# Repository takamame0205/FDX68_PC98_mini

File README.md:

# PC-98用 FDX68/FDD 簡易切り替えボード

<b>1. 概要</b><BR>
NECのPC-9800シリーズにGIMONS氏開発のフロッピーエミュレーターFDX68を接続し、実FDDと併用するための実験用ボードです。FDX68のエミュレーションモードおよびコントローラーモードをサポートしており、実FDDとしては3.5インチ(3モード可)×1台、あるいは3.5インチ1台+5インチ1台での使用を想定しています。ミカエル氏のFDS+と比べると低機能ですが、その分簡単に製作でき、DIP品のICのみで設計してあるのにもかかわらず小型化することができました。なお、このボードは私個人が研究目的で作成したもので開発途上のものです。ちなみにこちらでは、PC-9801BX3(CPUをDX4ODP-100MHzに換装)にFD1148TとFD1155Dを接続し、FDX68 Version 1.2A (fdrestore のみ 1.3)、RasPi OS buster 2021-01-11版使用にて動作確認を行っています。<br><br>

<b>2. 制限事項</b><BR>
このボードは簡素なつくりのため、FDS+と比べ機能制限が多いです。エミュレーションモードでのドライブ番号(0のみ、1のみ、0/1両方)はジャンパーで設定するようになっており、動的な変更はできません(もちろん、このジャンパーのピンヘッダ―に双極双投のトグルスイッチなどを接続すれば外部から切り替えることは可能です)。また、5インチドライブとして<b>ターミネーション抵抗値の低いFD1155Dなどを使用した場合に動作が不安定になる可能性</b>があります(対処法は下に記します)。<br><br>

<b>3. 免責など</b><br>
ここで公開している内容はありのまま(As Is)で提供するものであり、動作を保証するものではありません。また、使用したことによりお手持ちの機器(PC本体、FDX68、FDDなど)にダメージを与える可能性もあります。私個人が金銭的、身体的損害について補償することはできませんので、ご利用は個人の責任において行ってください。<br><br>
  
<b>4. ファイルの配置</b><BR>
KiCad : KiCadプロジェクトファイル<BR>
KiCad/garber : ガーバーファイル<BR>
Tiny13 : マイコン(ATtiny13A)のファームウェア(AtmelStudio用ソース)<BR>
Firmware : マイコン(ATtiny13A)のファームウェア(Intel Hex形式バイナリ)<BR>
　ヒューズ設定データはfuse.hex<BR>
　設定内容 : CKSEL = 01 (4.8MHz), CKDIV8 = 0 (600KHz)<br>
　　SUT = 10 (Slow Start), WDTON = 1 (WDT OFF)<br>
preview.png : 基板のプレビューイメージ<BR>
scheme.png : 基板回路図<BR><br>

<b>5. 部品一覧</b><br>
コネクター<br>
J1, J2：2.54mmピッチ 2x15pin ボックスヘッダー<br>
J3, J4：2.54mmピッチ 2x17pin ボックスヘッダー<br>
J5：2.54mmピッチ 5pin ライトアングルピンヘッダ―<br><br>
コンデンサー<br>
C1：47μF 25V アルミ電解コンデンサー<br>
C2, C3, C4：0.1μF 50V (積層)セラミックコンデンサー<br><br>
抵抗<br>
R1, R3：22kΩ<br>
R2：220Ω～270Ω (LEDの電流制限抵抗なので、使用するLEDによって適宜調整してください)<br><br>
IC<br>
  U1, U2：74HC4066 (<b>ON抵抗の低いもの</b>を選んでください)<br>
U3：ATtiny13A<br><br>
ダイオード<br>
D5, D6：BAT43 (Vfの小さいSBDを使用しています)<br><br>
ジャンパー<br>
JP2, 3：2.54mmピッチ 3pin ストレートピンヘッダー<br>
JP7：2.54mmピッチ 2pin ストレートピンヘッダー<br><br>

<b>6. 接続方法</b><BR>
マザーボードとの接続用(J1)および3.5インチFDD接続用(J2)のコネクターは30ピンタイプ(A-MateやFellowのマザーボードコネクターと同じタイプ)を、FDX68接続用(J3)および5インチFDD接続用(J4)のコネクターは34ピンタイプ(一般的なマザーボード上34ピンFDDコネクターと同じタイプ)を使用しています。いずれも左上(印のついている)ピンが1番ピンになっていますので、向きを間違えないように接続してください。J1, J3には<b>反転していない</b>ストレートのケーブルを使用します。FDX68のコネクターは一般的なPC-98用3.5インチFDDとは向きが逆になっていますので注意してください。マザーボードとの接続は、同じ30ピンのコネクターを搭載している機種であれば単純なストレートのケーブルでOKですが、34ピンのコネクター搭載機種だと変換ケーブルの作成が必要です。その場合、基板への電源供給ができませんので、変換ケーブルを作成する際にVCCピン(1,3,5)に電源を接続するか、操作スイッチなどを接続するJ5のVCC("+"表示のある1番ピン)から電源を供給するようにしてください。<BR><BR>
なお、J5(操作スイッチ接続コネクター)のピンアサインは下記のとおりです。<BR><BR>
Pin 1 (+) : VCC (J1のVCCピンと直結)<BR>
Pin 2 (L) : モード表示LED出力(Active Low)<BR>
Pin 3 (S) : 操作ボタン入力(Active Low)<BR>
Pin 4 (I) : RasPi電源検知入力(Active High)<BR>
Pin 5 (-) : GND<BR><BR>
モード表示LEDはアノードをVCC(Pin 1)に、カソードをLED出力(Pin 2)に接続します。電流制限抵抗は基板上にあるため(R2)外付けは不要です。また、操作ボタン(タクトスイッチなどでOKです)はボタン入力(Pin 4)とGND(Pin 5)の間に接続します。プルアップ抵抗などは不要です。Pin 4はFDX68(Raspberry Pi)の電源状態を検知して自動的にモードを切り替えるための入力で、Raspberry PiあるいはFDX68シールドの+5V端子を接続すればよいのですが、後述のジャンパー設定にてOPT2端子を検知に使用する場合には使用する必要はありません。また、電源検知機能を使用したくない場合にはソースコード settings.h の "#define PWRSENS 2" の行をコメントアウトしてコンパイルしてください。<BR><br>
 
<b>7. 設定用ジャンパー</b><br>
基板上のジャンパー(ピンヘッダー、はんだジャンパー)の一覧です。<br><br>
JP1 : PWR_SENS<br>
　電源検知機能を使用する場合に、検知用の信号をOPT2から取りたい場合にショートします。<br>
　FDX68のID設定を0,1とするとOPT2端子は電源ON時常にプルアップ状態になることを利用しています。<br>
JP2 : DS1 Select<br>
JP3 : DS0 Select<br>
　エミュレーションモード、およびノンエミュレーションモードにおいて、マザーボードからの<br>
　Drive select(DS) 0/1信号を3.5インチFDDとFDX68(or 5インチFDD)のどちらに接続するかを設定します。<br>
　コントローラーモードにおいてはマザーボードからのDS信号が切り離され、DS0/1いずれもFDX68に<br>
　直結されます。<br>
　FDX側をショートするとエミュレーションモードにおいて当該ドライブ番号側がエミュレートされます。<br>
　また、後述のノンエミュレーションモードにおいては5インチFDDが選択されるようになります。<br>
　3.5FD側をショートすると、当該ドライブ番号側は常に3.5インチFDDが選択されるようになります。<br>
JP4 : P4 SELECT (MS0)<br>
　FDX68のPin4を3.5インチFDDのMode Select(MS) 0に接続したい場合にショートします。<br>
　これを利用すると、3モードFDDを利用して1.44MBのFDのダンプ、リストアができるようになります。<br>
　この機能を利用して1.44MBのFDを扱うにはダンプ、リストア時に"-p4"オプションを指定すればOKです。<br>
　また、この機能は3.5インチFDD 0でのみ使用可能です(MS1には未接続のため)。<br>
JP6 : P4 SELECT (HL)<br>
　FDX68のPin4を5インチFDDのHead Load(HL)に接続し、コントローラーモード"-p4"オプションで<br>
　制御したい場合にショートします。<br>
　この基板では5インチFDDのHL端子をマザーボードと接続していませんので、通常はドライブ側でHL機能を<br>
　無効化してください。<br>
JP7 : HL<br>
　5インチFDDのPin4(HL/In Use)をGNDに落としたい場合にショートします。<br>
　HLを無効化したFDDでアクセスランプが点かない場合に、ショートすることにより点くようになることが<br>
　多いかと思います。<br>
  
<b>8. FDDタイプ別設定例</b><br>
以下にFDDのタイプ別の接続方法、設定方法を示します。PC-98用FDDでは2DDのディスクアクセス時に回転数が360rpmとなっており、他のシステムとは回転数が異なっています。FDX68のダンプ、リストアにおいては2D/2DDモードにおける回転数は300rpmであることが前提となっており、ドライブ側が360rpmで回転していることを検知するとエラーとなってしまいます。このため、2D/2DDモード時の回転数の設定ができる5インチFDDにおいては300rpmに設定する必要がありますが、その場合には本体側からの2DDディスクのアクセスはできなくなってしまいます。まだ一部の3モードFDDにおいては2DDモードで300rpmに設定できる(MS, Densityともアサートする)ことを確認しておりますが、その場合FDからのデータ読み込みエラーが多発しますし、書き込みはまずできない(読めないディスクができてしまう)ので、実用的ではありません。MSXにFD1231TやOSDを接続する実験においては、数台のドライブで試したところ、2DD/300rpmで読み込みが何とかできるものもありましたが、書き込みは全滅でした。ドライブの個体差にもよると思うのでものによってはダンプのみなら何とかできる可能性がありますが、基本的にはFDX68のコントローラーモードとPC-98用3.5インチFDDの組み合わせで2D/2DDディスクを扱うのは困難であると考えています。このような用途にはAT互換機用FDDを使う必要があるのかもしれません。<br><br>
<b>a. 3.5インチFDD×1台のみの場合</b><br>
26ピンのFDD(FD1138Tなど)であればA-Mate, Fellowなどに使用されている30ピン-26ピンケーブルで接続しますが、34ピンコネクターを持つFDD(FD1231Tなど)では変換ケーブルが必要となります。2股ケーブルを使用することによりDrive0, Drive1いずれにも設定可能です。JP2/3はFDDに設定したドライブ番号側を3.5FDに、そうでない側をFDXに設定します。<br><br>
<b>b. 3.5インチFDD×2台の場合(1)</b><br>
2股ケーブルを使用することで2台ともJ2に接続することも可能ですが、その場合機能の組み合わせに制限が生じます。<br>
JP2/3を3.5FD側に設定したドライブ番号：本体から認識可能　エミュレーション利用不可<br>
JP2/3をFDX側に設定したドライブ番号：本体から認識不可　エミュレーション利用可能<br>
いずれのドライブもコントローラーモードでFDX68側から制御することは可能です("-i"オプションでドライブ番号を指定)<br><br>
<b>c. 3.5インチFDD×2台の場合(2)</b><br>
応用として、あえて片方をJ4(5インチFDD接続用)に接続するという方法があります。J4に接続したドライブは3モードでの利用はできませんが、ノンエミュレーションモードにて2ドライブとも本体から認識可能となります。この方法を利用する場合、HL機構を持たないドライブではJP7はオープンでよいと思います。接続ケーブルはFD1231Tなどで使用されている、マザーボード側とFDD側でコネクターの向きが反転したケーブルでよいと思いますが、FDD側のコネクターの向きをよく確認するようにしてください。また、3モードFDDを使用する場合にはケーブルの1番ピンをカットする必要があります(結果的に1.44MBの2HDディスクは利用できなくなります)。JP2/JP3設定は下記のようにします。<br>
J2に接続したドライブ(DS0/1)を3.5FD側に設定、J4に接続したドライブ(DS1/0)をFDX側に設定<br>
以上の設定で、ノンエミュレーションモードでは2台ともアクセス可能、エミュレーションモードではJ2側のFDD+FDX68、コントローラーモードでは2台とも制御可能となります。<br><br>
<b>d. 3.5インチFDD×1台+5インチFDD×1台の場合</b><br>
もともとこの基板はこの組み合わせて使用することを想定して設計し、動作確認もOSD-U(あるいはFD1148T)とFD1155Dを各1台接続して行っています。基本的な設定、接続はc.と同じですが、ケーブルを用意するにあたっては5インチFDDのコネクターの向きに注意してください。以下に動作確認済み5インチFDDにおけるジャンパー設定内容を示します。なお、上記のとおりFDX68では2D/2DDのディスクは300rpmで使用することが前提となっているため、下記の設定ではそうしています(HDE=2)。ただし、その場合にはノンエミュレーションモードにて本体から2D/2DDディスクを読み書きすることはできなくなります。また、FD1155Dなどのターミネーション抵抗値が小さい(FD1155Dの場合は330Ω)ドライブを使用すると、DS信号などのLレベル電圧が高めになってしまい「制限事項」の欄に記したとおり動作が不安定になることがあります(ドライブが認識されなかったり、アクセスできなかったりなど)。この場合にはFDX68のターミネーション抵抗(RN1-3)を除去すると動作することが多いかと思いますが、OPT2による電源検知が効かなくなります。ターミネーション抵抗を除去した状態で電源検知を利用したい場合にはOPT2のみプルアップすればOKです。<br><br>
FD1155(無印)<BR>
　DX=ドライブ番号 USE=2 MON=1 HS=1 LED=1+5<br>
　本基板上のJP7はショートしておいてください<br>
FD1155D(タイプ1)<br>
　USEジャンパーを2にした場合にアクセスランプが点灯しなくなるタイプはこちら<br>
　DX=ドライブ番号 USE=2 MON=1 RD=1 DCG=1 HDE=2 DEN=1<br>
　本基板上のJP7をショートするとアクセスランプが点灯するようになります<br>
　JP7をショートするとアクセスしていないときにもうっすらと点灯する場合がありますが、<br>
　これは故障ではありません。<br>
　(アクセスしていないときにも一定間隔でDS信号がアサートされている場合があるため)<br>
FD1155D(タイプ2)<br>
　USEジャンパーを2にした場合にもアクセスランプが適切に点灯するタイプはこちら<br>
　DX=ドライブ番号 USE=2 MON=1 <b>RD=2</b> DCG=1 HDE=2 DEN=1<br>
　RDジャンパーを2に設定することによりFDDに内蔵のVFOが有効化されてしまいますが<br>
　このように設定しないとコントローラーモードでのリストアに失敗します<br>
　RD=2にするとダンプ及び本体からのアクセスができなくなりますが、<br>
　J4のPin 3/7/11をGNDとショートすることによりVFOが無効化されアクセスできるようになります<br>
　(特にジャンパーなどは設けていませんので、手配線で3-5-7-9-11をすべてショートしてください。)<br>
　また、当方で確認した限りではGNDにショートしてもリストア動作に支障はありませんでした<br><br>
このほかにも接続方法はいろいろと考えられます。回路図や下記の各モードでの動作をご理解のうえご検討いただければと思います。<br><br>

<b>9. 動作モード</b><br>
この基板には以下の3つの動作モードがあります。それぞれの動作および信号線の切り替え内容について解説します。切り替えを行っているのはDS0/1, Motor On(MON), Readyのみで、基本的に他の信号線は直結してあります(MS0/1およびHLはマザーボード-3.5インチFDD間のみ)。<br><br>
<b>a. ノンエミュレーションモード(LED消灯)</b><br>
DS0/1, MON, Readyがマザーボード－3.5インチFDD－5インチFDD(－FDX68)まですべて直結されます。結果として3.5インチFDD, 5インチFDDともに本体から通常通りアクセスできるようになります。このモードではFDX68の電源が入っていると誤動作する可能性があるので、FDX68の電源を切った状態で使用してください。<br><br>
<b>b. エミュレーションモード(LED点灯)</b><br>
MON, Readyがマザーボード－3.5インチFDD－FDX68まで接続され、5インチFDDは切り離されます。DS0/1はJP2/3によって接続先が設定されます。結果として3.5インチFDD, およびFDX68が本体からアクセスできるようになります。ドライブ0/1のどちらにFDD, FDX68を割り当てるかをJP2/3を用いて設定します。<br><br>
<b>c. コントローラーモード(LED点滅)</b><br>
DS0/1, MON, Readyが3.5インチFDD－FDX68－5インチFDDまで接続され、マザーボードは切り離されます。結果として3.5インチFDD, および5インチFDDがFDX68からアクセスできるようになり、ダンプ、リストア操作が可能となります。<br><br>
  
<b>10. 基本的な操作方法</b><br>
初回起動時(電源ON時)には、FDX68の電源が入っておればエミュレーションモード、入っていなければノンエミュレーションモードで起動します。その後は下記の操作でモードの切り替えが可能です。<br><br>
操作ボタン短押し：エミュレーションモード←→コントローラーモードの切り替え(トグル)<br>
操作ボタン長押し：ノンエミュレーションモードに切り替え(約3秒、LEDが一瞬点滅するまで押してください)<br>
FDX68 電源ON：エミュレーションモードに切り替え<br>
FDX68 電源OFF：ノンエミュレーションモードに切り替え<br><br>

<b>11. 既知の問題点</b><br>
a. 概ね設計どおりの動作を確認してはいますが、 こちらの動作確認環境(PC-9801BX3+OSD)では1.44MBモードでの動作がやや不安定です。具体的には、エミュレーションモードにて1.44MBのイメージをマウントし、そのイメージに書き込むと読めないセクターができてしまうことがありました。また、1.44MBのディスクのダンプは特に問題なくできましたが、リストアを行うと一部にエラーのあるディスクができてしまうことがありました。このボードの設計というよりは、FDDやマザーボードとFDX68の相性なのかもしれないと考えています。<br>
b. FDX68は本来電源OFFの状態で接続されることを想定していません。環境によっては動作が不安定になる(FDDが本体から4台見えてしまう、3モードFDDの動作がおかしくなる)場合があることを確認しています。これはおそらくFDX68シールドのターミネーション抵抗(プルアップ抵抗)を経由してシールド上のロジックICに中途半端な電圧で給電されてしまうことが原因ではないかと考えています。対策としてはターミネーション抵抗(RN1-3)を装着しない、抵抗値を高くする、コモン端子にダイオードを挟んで接続するなどの方法で解決できる可能性があります。こちらでも試しにターミネーション抵抗を除去してみたところ、上記のような現象は見られなくなりました。ただしこの場合、ケーブルは極力短くしなければ動作が不安定になる可能性があります。<br>
c. 繰り返しになりますが、FD1155Dなどを接続した場合にドライブが認識されない場合があります。この場合にもターミネーション抵抗の除去が有効な場合があります。<br>
  
このボードの開発中に実施した各種の実験や、FDX68に関連したツイートを下記にまとめております。興味のある方はご覧ください。
https://min.togetter.com/ba5qN4b

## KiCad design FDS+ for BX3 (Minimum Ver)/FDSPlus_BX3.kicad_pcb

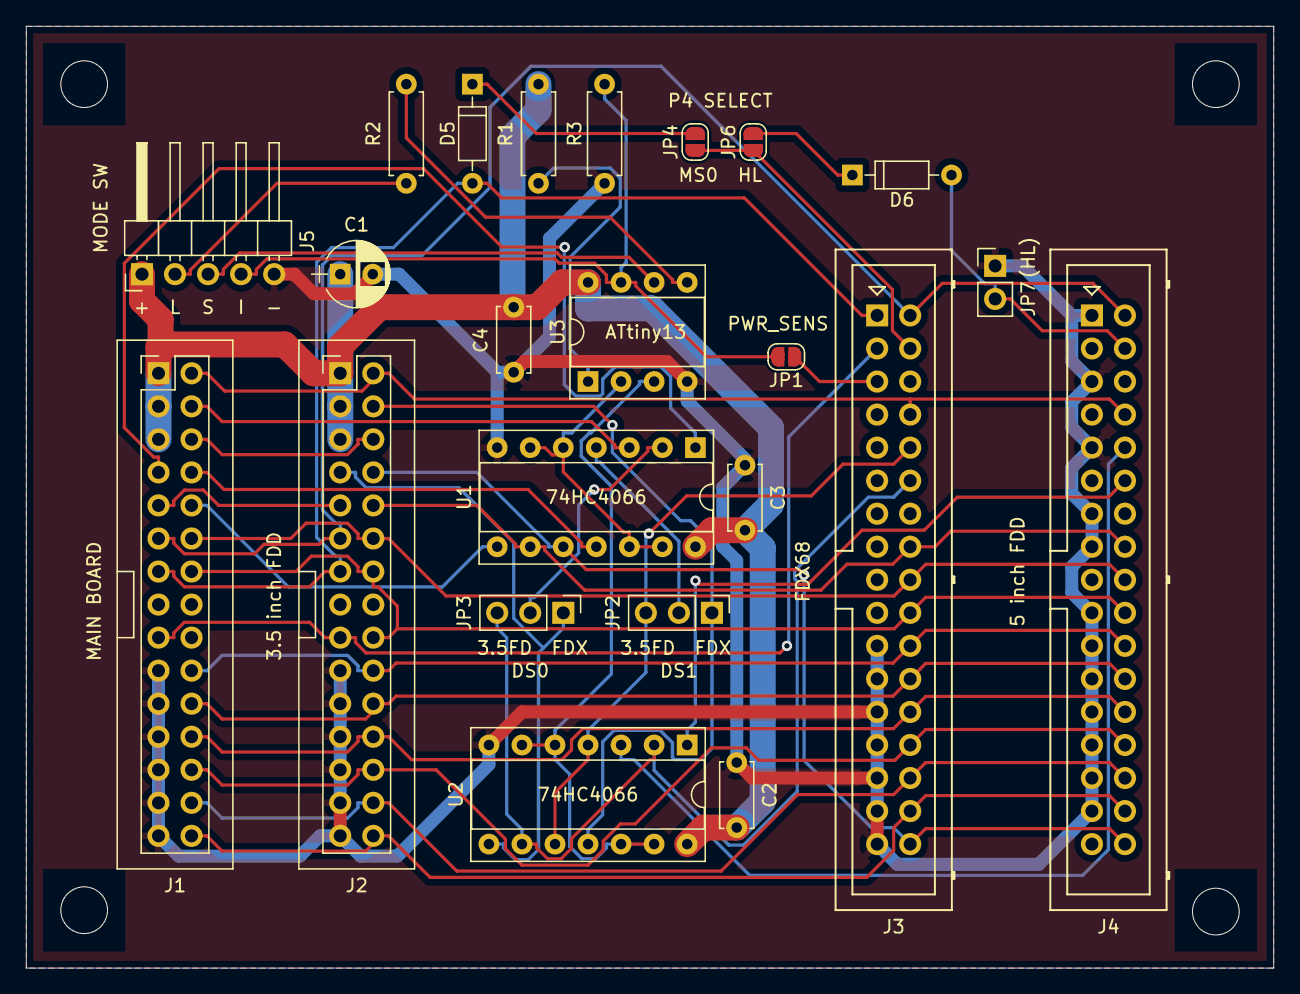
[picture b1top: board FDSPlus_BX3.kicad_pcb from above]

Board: 2 copper layers, 95.9 x 72.4 mm, 23 parts (0 on the bottom side), 42 nets.

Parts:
C1: 47; CP_Radial_D5.0mm_P2.50mm
C2, C3, C4: 0.1; C_Disc_D5.0mm_W2.5mm_P5.00mm
D5, D6: BAT43; D_DO-35_SOD27_P7.62mm_Horizontal
J1: M/B; Pin_Header_Straight_2x15_Pitch2.54mm
J2: 3.5FDD; Pin_Header_Straight_2x15_Pitch2.54mm
J3: FDX68; Multicomp_MC9A12-3434_2x17x2.54mm_Straight
J4: 5FDD; Multicomp_MC9A12-3434_2x17x2.54mm_Straight
J5: SW; Pin_Header_Angled_1x05_Pitch2.54mm
JP1: PWR_SENS; SolderJumper-2_P1.3mm_Open_RoundedPad1.0x1.5mm
JP2: DS0_SEL; Pin_Header_Straight_1x03_Pitch2.54mm
JP3: DS1_SEL; Pin_Header_Straight_1x03_Pitch2.54mm
JP4: P4_TO_MS; SolderJumper-2_P1.3mm_Open_RoundedPad1.0x1.5mm
JP6: P4_TO_HL; SolderJumper-2_P1.3mm_Open_RoundedPad1.0x1.5mm
JP7: FORCE_HL; Pin_Header_Straight_1x02_Pitch2.54mm
R1, R3: 22k; R_Axial_DIN0207_L6.3mm_D2.5mm_P7.62mm_Horizontal
R2: 220; R_Axial_DIN0207_L6.3mm_D2.5mm_P7.62mm_Horizontal
U1, U2: 74HC4066; DIP-14_W7.62mm_Socket
U3: ATtiny13A-PU; DIP-8_W7.62mm_Socket

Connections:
+5V: C1.1, C2.1, C3.1, C4.1, J1.1, J1.3, J1.5, J2.1, J2.3, J2.5, J5.1, R1.2, U1.14, U2.14, U3.8
/CTL_MODE: U2.5, U2.6, U2.12, U2.13, U3.3
/DCHG: J1.6, J2.6
/DEN: J1.11, J2.11, J3.2, J4.2
/DIR: J1.12, J2.12, J3.18, J4.18
/DS1INH: J5.4, JP1.2, R3.2, U3.7
/D_DS0: J4.10, U2.3
/D_DS1: J4.12, U2.1
/D_HL: D6.2, J4.4, JP7.2
/D_MON: J2.10, J3.16, J4.16, U1.9
/D_RDY: J2.8, J3.34, J4.34, U1.10
/EM_MODE: U1.5, U1.6, U1.12, U1.13, U3.2
/F_DS0: J2.4, JP2.1, U2.11
/F_DS1: J2.7, JP3.1, U2.8
/F_HL: J1.9, J2.9
/F_MS0: D5.2, J1.13, J2.13, J3.1
/F_MS1: J1.17, J2.17, J3.3
/IDX: J1.2, J2.2, J3.8, J4.8
/LED: J5.2, R2.2
/M_DS0: J1.4, U1.3
/M_DS1: J1.7, U1.1
/M_MON: J1.10, U1.8
/M_RDY: J1.8, U1.11
/M_SW: J5.3, U3.6
/OPT2: J3.5, JP1.1
/RD: J1.28, J2.28, J3.30, J4.30
/SIDE: J1.30, J2.30, J3.32, J4.32
/STEP: J1.14, J2.14, J2.18, J3.20, J4.20
/T00: J1.24, J2.24, J3.26, J4.26
/WD: J1.20, J2.20, J3.22, J4.22
/WG: J1.22, J2.22, J3.24, J4.24
/WP: J1.26, J2.26, J3.28, J4.28
/X_DS0: J3.10, JP2.3, U2.4, U2.10
/X_DS1: J3.12, JP3.3, U2.2, U2.9
/X_PIN4: J3.4, JP4.2, JP6.1
GND: C1.2, C2.2, C3.2, C4.2, J1.19, J1.21, J1.23, J1.25, J1.27, J1.29, J2.19, J2.21, J2.23, J2.25, J2.27, J2.29, J3.21, J3.23, J3.25, J3.27, J3.29, J3.31, J3.33, J4.1, J4.5, J4.9, J4.13, J4.15, J4.19, J4.21, J4.23, J4.25, J4.27, J4.29, J4.31, J5.5, JP7.1, R3.1, U1.7, U2.7, U3.4
unnamed: D5.1, JP4.1
unnamed: D6.1, JP6.2
unnamed: JP2.2, U1.4
unnamed: JP3.2, U1.2
unnamed: R1.1, U3.1
unnamed: R2.1, U3.5

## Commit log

2022-01-22 Add Values
